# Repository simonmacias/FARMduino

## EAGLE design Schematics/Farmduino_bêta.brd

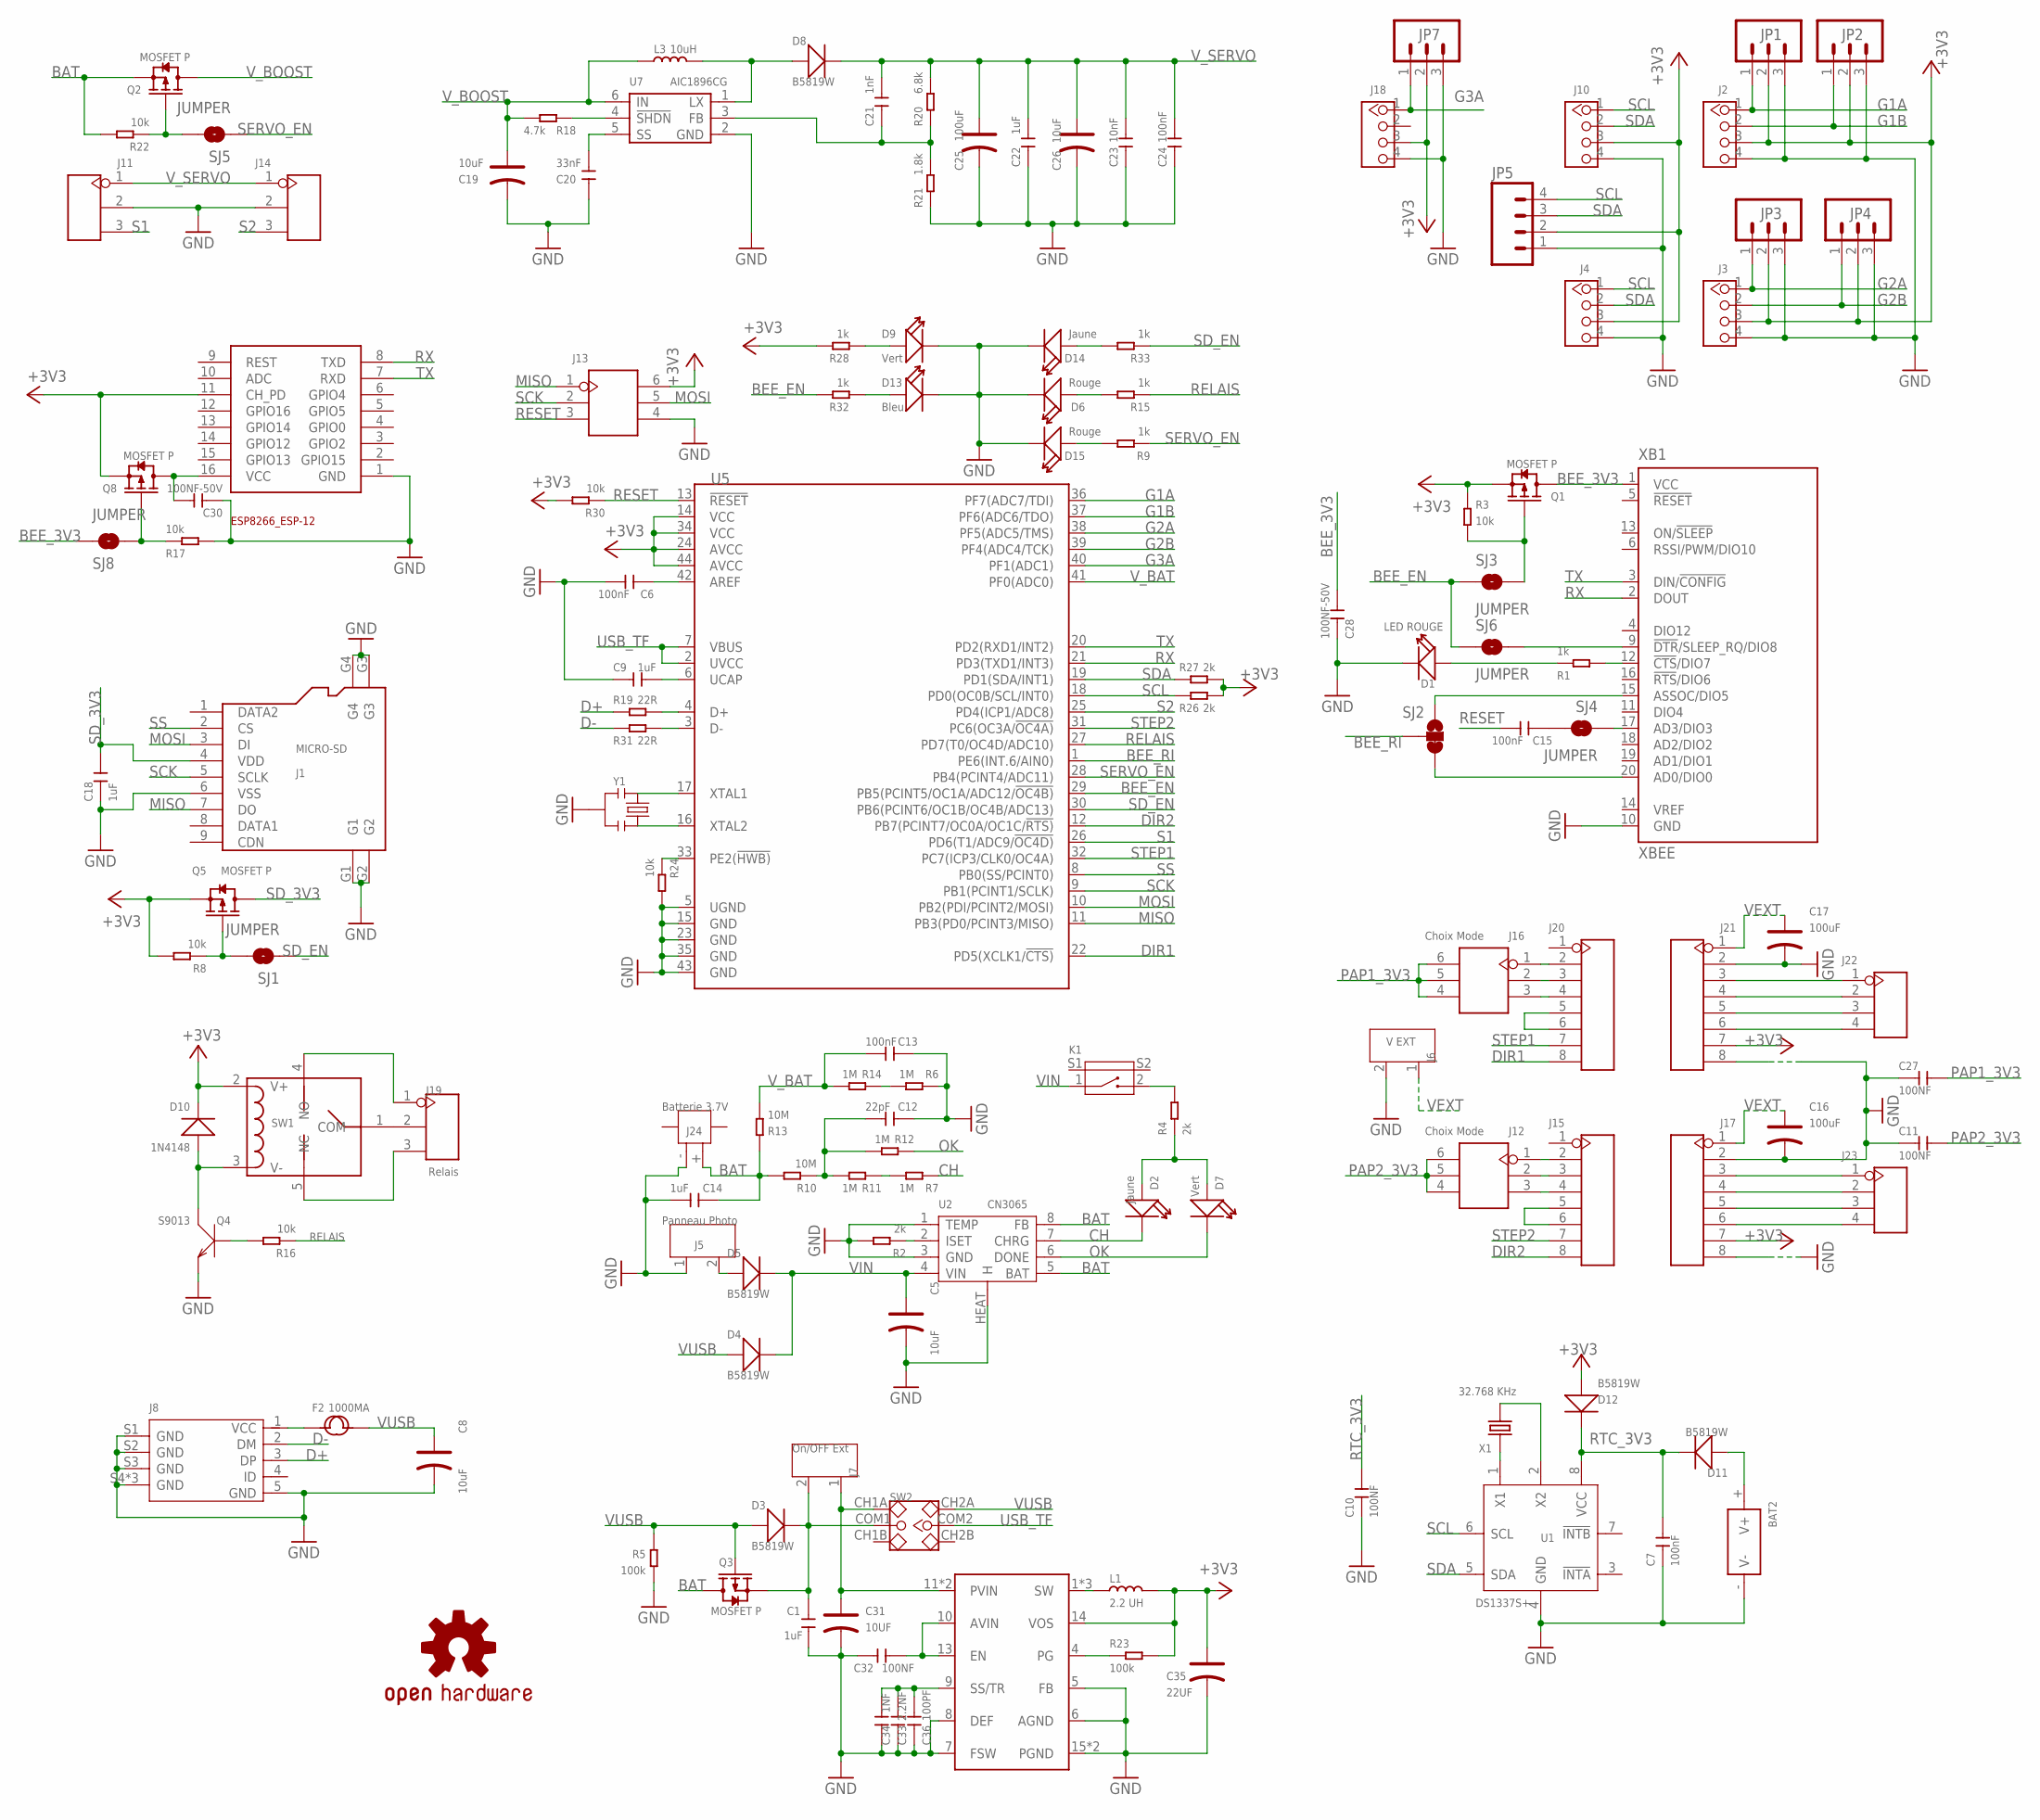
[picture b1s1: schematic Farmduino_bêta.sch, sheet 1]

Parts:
BAT2: SMD-BATTERY-CELL-HOLDER-PLASTIC; BAT2P-SMD-16.4-CR1220
C1, C14, C18, C22: 1uF; C0805; MPN 02016D105MAT2A
C5, C8: 10uF; AVX-A; MPN 06036D106MAT2A
C6, C7, C13, C15, C24: 100nF; C0805; MPN 0402ZD104KAT2A
C9: 1uF; C0805
C10, C11, C27, C32: 100NF; C0805
C12: 22pF; C0805
C16, C17: 100uF; ELECTRO-SMD-C-6MM; MPN 06036D106MAT2A
C19, C26: 10uF; AVX-A
C20: 33nF; C0603
C21: 1nF; C0603
C23: 10nF; C0805
C25: 100uF; AVX-B
C28, C30: 100NF-50V; C0805
C31: 10UF; AVX-A
C33: 2.2NF; C0603
C34: 1NF; C0603
C35: 22UF; AVX-B
C36: 100PF; C0603
D1: LED ROUGE; LED-0603
D2: Jaune; LED-0805
D3, D4, D5, D8, D11, D12: B5819W; SOD-123
D6, D15: Rouge; LED-0603
D7: Vert; LED-0805
D9: Vert; LED-0603
D10: 1N4148; LL-34
D13: Bleu; LED-0603
D14: Jaune; LED-0603
F2: 1000MA; F1206
J1: MICRO-SD; MICRO-SD9+4P-SMD-16.1X14.5X1.85MM
J2, J3, J4, J10, J18: GROVE-CONNECTOR-DIP(4P-2.0); HW4-2.0
J5: Panneau Photo; H2-3.5-7.0X7.0MM; MPN 1776275-2
J6: V EXT; H2-3.5-7.0X7.0MM; MPN 1776275-2
J7: On/OFF Ext; H2-3.5-7.0X7.0MM
J8: MICRO-USB-SMD-B-WITHOUT-POST-W/P(ST-USB-001G); MICRO-USB5+4P-SMD-0.65-B
J11, J14: DIP-WHITE-MALE-HEADER-VERT(3P-2.54); H3-2.54
J12, J16: Choix Mode; H2X3-2.54
J13: DIP-BLACK-MALE-HEADER（2X3P-2.54）-2.54; H2X3-2.54
J15, J17, J20, J21: DIP-YELLOW-FEMALE-HEADER(8P-2.54); H8-2.54
J19: Relais; H3-5.0-15.5X8.0MM
J22, J23: DIP-BLACK-MALE-HEADER-VERT(4P-2.54); H4-2.54
J24: Batterie 3.7V; HW2-SMD-1.0-90D
JP1, JP2, JP3, JP4, JP7: M03SCREW; SCREWTERMINAL-3.5MM-3
JP5: M04SCREW; SCREWTERMINAL-3.5MM-4
K1: SMD-BUTTON-2+2P; SW4-SMD-7.0X3.5X3.5MM-90D
L1: 2.2 UH; L0805
L3: 10uH; L1210
LOGO1: OSHW-LOGOM; OSHW-LOGO-M
Q1, Q2, Q3, Q5, Q8: MOSFET P; SOT-23
Q4: S9013; SOT-23
R1, R9, R15, R28, R32, R33: 1k; R0805
R2, R4, R27: 2k; R0805
R3, R8, R16, R17, R22, R24, R30: 10k; R0805
R5, R23: 100k; R0805
R6, R7, R11, R14: 1M; R0402
R10, R13: 10M; R0603
R12: 1M; R0805
R18: 4.7k; R0805
R19, R31: 22R; R0805
R20: 6.8k; R0603
R21: 1.8k; R0603
R26: 2k; R0603
SJ1, SJ3, SJ4, SJ5, SJ6, SJ8: JUMPER; PAD-JUMPER-2-NO_NO_SILK
SJ2: JUMPER-PAD-3-2OF3_NC_BY_TRACE_LARGE; PAD-JUMPER-3-2OF3_NC_BY_TRACE_YES_SILK_LARGE
SW1: RELAY-HLS8L-DC3V-S-C(5P-19X15MM); REY5-19.0X15.0X15.0MM
SW2: DIP-TOGGLE-SWITCH-2CH-(2X3P-90D); SW6-2.54-9.0X3.5X3.2MM-90D
U1: DS1337S+; SOIC8-1.27-5X4MM
U2: CN3065; DFN8G-0.5-3X3MM
U3: TPS62132RGTR; QFN16G-0.5-3X3MM
U5: MCU-ATMEGA32U4(TQFP44)-AU; TQFP44-0.8-9.6X9.6MM
U7: AIC1896CG; SOT-23-6
U$1: ESP8266_ESP-12; ESP8266-ESP12
X1: 32.768 KHz; X2-SMD-3.2X1.5X0.55MM
XB1: XBEE
Y1: SMD-CRYSTAL-8MHZ--0.3%-150R(3P-3.6X1.3MM); X3-SMD-3.6X1.3X0.8MM

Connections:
!SHDN: R18.2, U7.4 (!SHDN)
+3V3: C35.+, D10.C (-), D12.+, J2.3, J3.3, J4.3, J10.3, J13.6, J17.7, J18.3, J21.7, JP1.2, JP2.2, JP3.2, JP4.2, JP5.2, JP7.2, L1.2, Q1.2 (S), Q5.2 (S), Q8.2 (S), R3.1, R8.2, R23.2, R26.1, R27.1, R28.2, R30.2, SW1.2 (V+), U3.14 (VOS), U5.14 (VCC), U5.24 (AVCC), U5.34 (VCC), U5.44 (AVCC), U$1.11 (CH_PD)
A7: C12.1, R10.1, R11.2, R12.2
BAT: C14.2, J24.+ (1), Q2.2 (S), Q3.3 (D), R10.2, R13.2, R22.2, U2.5 (BAT), U2.8 (FB)
BEE_3V3: C28.2, Q1.3 (D), SJ8.1, XB1.1 (VCC)
BEE_CTS: R1.2, XB1.12 (!CTS!/DIO7)
BEE_EN: R32.2, SJ3.1, SJ6.1, U5.29 (PB5(PCINT5/OC1A/ADC12/!OC4B))
BEE_RI: SJ2.2, U5.1 (PE6(INT.6/AIN0))
CH: D2.-, R7.1, U2.7 (CHRG)
D6: D1.+, R1.1
D+: J8.3 (DP), R19.1
D-: J8.2 (DM), R31.1
DIR1: J20.8, U5.22 (PD5(XCLK1/!CTS))
DIR2: J15.8, U5.12 (PB7(PCINT7/OC0A/OC1C/!RTS))
G1A: J2.1, JP1.1, U5.36 (PF7(ADC7/TDI))
G1B: J2.2, JP2.1, U5.37 (PF6(ADC6/TDO))
G2A: J3.1, JP3.1, U5.38 (PF5(ADC5/TMS))
G2B: J3.2, JP4.1, U5.39 (PF4(ADC4/TCK))
G3A: J18.1, JP7.1, U5.40 (PF1(ADC1))
GND: BAT2.- (V-), C1.1, C5.-, C6.2, C7.1, C8.-, C9.2, C10.1, C11.1, C12.2, C13.2, C14.1, C16.-, C17.-, C18.1, C19.-, C20.1, C22.1, C23.1, C24.1, C25.-, C26.-, C27.1, C28.1, C30.1, C31.-, C32.2, C33.1, C34.1, C35.-, C36.1, D1.-, D6.-, D9.-, D13.-, D14.-, D15.-, J1.6 (VSS), J1.G1, J1.G2, J1.G3, J1.G4, J2.4, J3.4, J4.4, J5.1, J6.2, J8.5 (GND), J8.S1 (GND), J8.S2 (GND), J8.S3 (GND), J8.S4 (GND), J8.S5 (GND), J8.S6 (GND), J10.4, J11.2, J13.4, J14.2, J17.2, J17.8, J18.4, J21.2, J21.8, J24.- (2), JP1.3, JP2.3, JP3.3, JP4.3, JP5.1, JP7.3, Q4.2 (E), R2.2, R5.1, R6.1, R17.2, R21.1, R24.2, U1.4 (GND), U2.1 (TEMP), U2.3 (GND), U2.HEAT (H), U3.5 (FB), U3.6 (AGND), U3.7 (FSW), U3.8 (DEF), U3.15 (PGND), U3.16 (PGND), U5.5 (UGND), U5.15 (GND), U5.23 (GND), U5.35 (GND), U5.43 (GND), U7.2 (GND), U$1.1 (GND), XB1.10 (GND), Y1.2
MISO: J1.7 (DO), J13.1, U5.11 (PB3(PD0/PCINT3/MISO))
MOSI: J1.3 (DI), J13.5, U5.10 (PB2(PDI/PCINT2/MOSI))
unnamed: K1.2, R4.2
unnamed: J15.5, J15.6
unnamed: D9.+, R28.1
unnamed: SJ4.1, XB1.17 (AD3/DIO3)
unnamed: D13.+, R32.1
unnamed: SJ2.1, XB1.15 (ASSOC/DIO5)
unnamed: SJ2.3, XB1.20 (AD0/DIO0)
unnamed: R2.1, U2.2 (ISET)
unnamed: U1.1 (X1), X1.1
unnamed: U1.2 (X2), X1.2
unnamed: C15.2, SJ4.2
unnamed: U5.16 (XTAL2), Y1.3
unnamed: BAT2.+ (V+), D11.+
unnamed: R6.2, R14.1
unnamed: D2.+, D7.+, R4.1
unnamed: D5.+, J5.2
unnamed: R7.2, R11.1
unnamed: Q1.1 (G), R3.2, SJ3.2
unnamed: C1.2, D3.-, J7.2, Q3.2 (S), SW2.COM1
unnamed: C31.+, J7.1, SW2.CH1A, U3.11 (PVIN), U3.12 (PVIN)
unnamed: Q5.1 (G), R8.1, SJ1.2
unnamed: C30.2, Q8.3 (D), U$1.16 (VCC)
unnamed: C20.2, U7.5 (SS)
unnamed: D8.+, L3.2, U7.1 (LX)
unnamed: C21.1, R20.1, R21.2, U7.3 (FB)
unnamed: Q2.1 (G), R22.1, SJ5.2
unnamed: J16.3, J20.4
unnamed: J16.2, J20.3
unnamed: D14.+, R33.2
unnamed: J16.1, J20.2
unnamed: J12.3, J15.4
unnamed: J12.2, J15.3
unnamed: R24.1, U5.33 (PE2(!HWB))
unnamed: R31.2, U5.3 (D-)
unnamed: C9.1, U5.6 (UCAP)
unnamed: F2.1, J8.1 (VCC)
unnamed: D6.+, R15.2
unnamed: J12.1, J15.2
unnamed: J20.5, J20.6
unnamed: Q8.1 (G), R17.1, SJ8.2
unnamed: R19.2, U5.4 (D+)
unnamed: SJ6.2, XB1.9 (!DTR!/SLEEP_RQ/DIO8)
unnamed: R23.1, U3.4 (PG)
unnamed: D15.+, R9.2
unnamed: J17.3, J23.1
unnamed: J17.4, J23.2
unnamed: J17.5, J23.3
unnamed: J17.6, J23.4
unnamed: C33.2, C34.2, C36.2, U3.9 (SS/TR)
unnamed: L1.1, U3.1 (SW), U3.2 (SW), U3.3 (SW)
unnamed: J21.3, J22.1
unnamed: J21.4, J22.2
unnamed: J21.5, J22.3
unnamed: J21.6, J22.4
unnamed: Q4.1 (B), R16.2
unnamed: D10.A (+), Q4.3 (C), SW1.3 (V-)
unnamed: J19.2, SW1.1 (COM)
unnamed: C32.1, U3.10 (AVIN), U3.13 (EN)
unnamed: U5.17 (XTAL1), Y1.1
unnamed: C6.1, U5.42 (AREF)
NC1: J19.3, SW1.5 (NC)
NO1: J19.1, SW1.4 (NO)
OK: D7.-, R12.1, U2.6 (DONE)
PAP1_3V3: C27.2, J16.4, J16.5, J16.6
PAP2_3V3: C11.2, J12.4, J12.5, J12.6
RELAIS: R15.1, R16.1, U5.27 (PD7(T0/OC4D/ADC10))
RESET: C15.1, J13.3, R30.1, U5.13 (!RESET)
RTC_3V3: C7.2, C10.2, D11.-, D12.-, U1.8 (VCC)
RX: U5.21 (PD3(TXD1/INT3)), U$1.8 (TXD), XB1.2 (DOUT)
S1: J11.3, U5.26 (PD6(T1/ADC9/!OC4D))
S2: J14.3, U5.25 (PD4(ICP1/ADC8))
SCK: J1.5 (SCLK), J13.2, U5.9 (PB1(PCINT1/SCLK))
SCL: J4.1, J10.1, JP5.4, R26.2, U1.6 (SCL), U5.18 (PD0(OC0B/SCL/INT0))
SDA: J4.2, J10.2, JP5.3, R27.2, U1.5 (SDA), U5.19 (PD1(SDA/INT1))
SD_3V3: C18.2, J1.4 (VDD), Q5.3 (D)
SD_EN: R33.1, SJ1.1, U5.30 (PB6(PCINT6/OC1B/OC4B/ADC13))
SERVO_EN: R9.1, SJ5.1, U5.28 (PB4(PCINT4/ADC11))
SS: J1.2 (CS), U5.8 (PB0(SS/PCINT0))
STEP1: J20.7, U5.32 (PC7(ICP3/CLK0/OC4A))
STEP2: J15.7, U5.31 (PC6(OC3A/!OC4A))
TX: U5.20 (PD2(RXD1/INT2)), U$1.7 (RXD), XB1.3 (DIN/!CONFIG)
USB_TF: SW2.COM2, U5.2 (UVCC), U5.7 (VBUS)
VEXT: C16.+, C17.+, J6.1, J17.1, J21.1
VIN: C5.+, D4.-, D5.-, K1.1, U2.4 (VIN)
VUSB: C8.+, D3.+, D4.+, F2.2, Q3.1 (G), R5.2, SW2.CH2A
V_BAT: C13.1, R13.1, R14.2, U5.41 (PF0(ADC0))
V_BOOST: C19.+, L3.1, Q2.3 (D), R18.1, U7.6 (IN)
V_SERVO: C21.2, C22.2, C23.2, C24.2, C25.+, C26.+, D8.-, J11.1, J14.1, R20.2

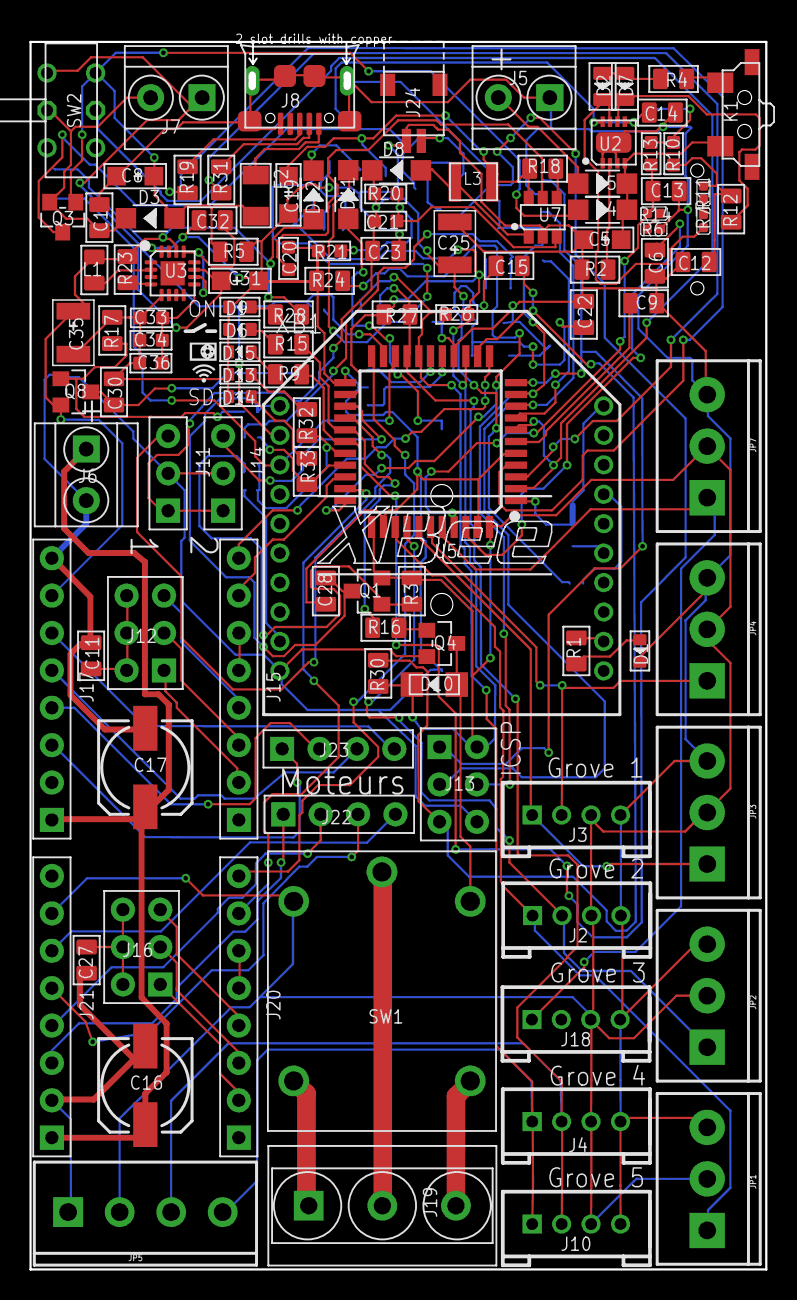
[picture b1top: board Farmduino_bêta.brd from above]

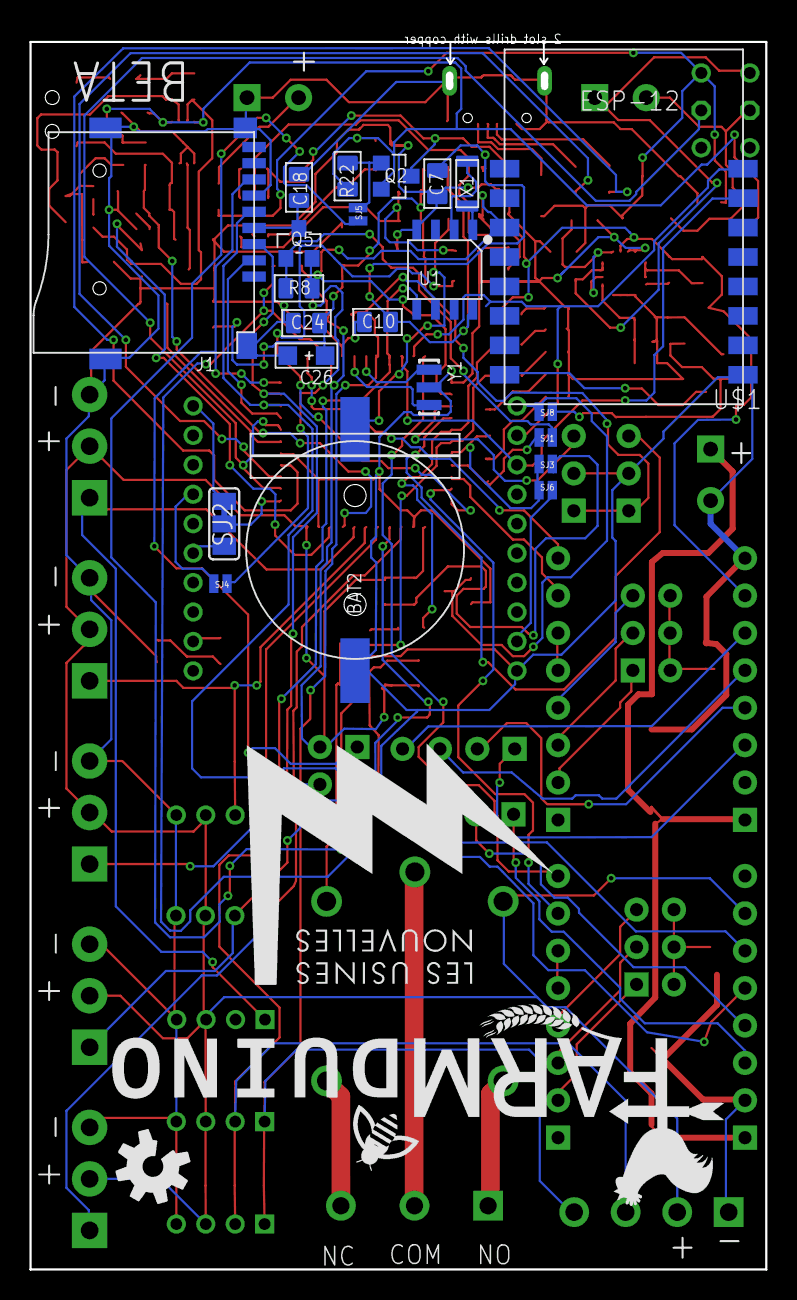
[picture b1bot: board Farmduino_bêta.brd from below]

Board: 2 copper layers, 50.0 x 83.4 mm, 137 parts (23 on the bottom side), 110 nets.

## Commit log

2015-06-23 Create Schematics

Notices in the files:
parts and their libraries:
SparkFun-Connectors: Licensing: Creative Commons ShareAlike 4.0 International - https://creativecommons.org/licenses/by-sa/4.0
